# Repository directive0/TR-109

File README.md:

#
This repository hosts a set of design documents for the TR-109 Mark I Picorder. A Picorder is a Raspberry Pi based handheld device that records and displays sensor data for immediate analysis. The TR-109 is designed to use a Raspberry Pi Zero W, a set of custom designed PCBs, and a 3D printed enclosure to achieve this goal. This project, along with [PicorderOS](https://squaredwave.com/wiki/index.php?title=PicorderOS) attempts to be a single self contained solution for anyone wishing to produce their own Picorder.

## What is included:

- The enclosure_design folder contains the .blend file used to produce the STLs for the case, diffusers and spacers. It also contains the main STLs ready to be printed, and an svg file to produce your own stickers.

- The pcb_design folder contains KiCad 5.1.10 files of both the main board, sensor board and indicator board pcbs. These files can be used to produce and test PCBs. There is some PCBWay files that may be useful with their Assembly service, but this is not finalized and may not work properly.

## What is not yet included:

- There are no assembly instructions. I hope to produce some in the future.

While it is not required, if you make a picorder using this repository I would appreciate you sharing photos or videos your build with me at chris@squaredwave.com.

For a more regularly updated description of this project please visit the [wiki](https://squaredwave.com/wiki/index.php?title=Picorder_2)

Originally designed by Chris Barrett in 2021. I consider this project to be "Open Hardware", and as such is free to use, modify distribute or sell. It comes with no promise of support or warranty.

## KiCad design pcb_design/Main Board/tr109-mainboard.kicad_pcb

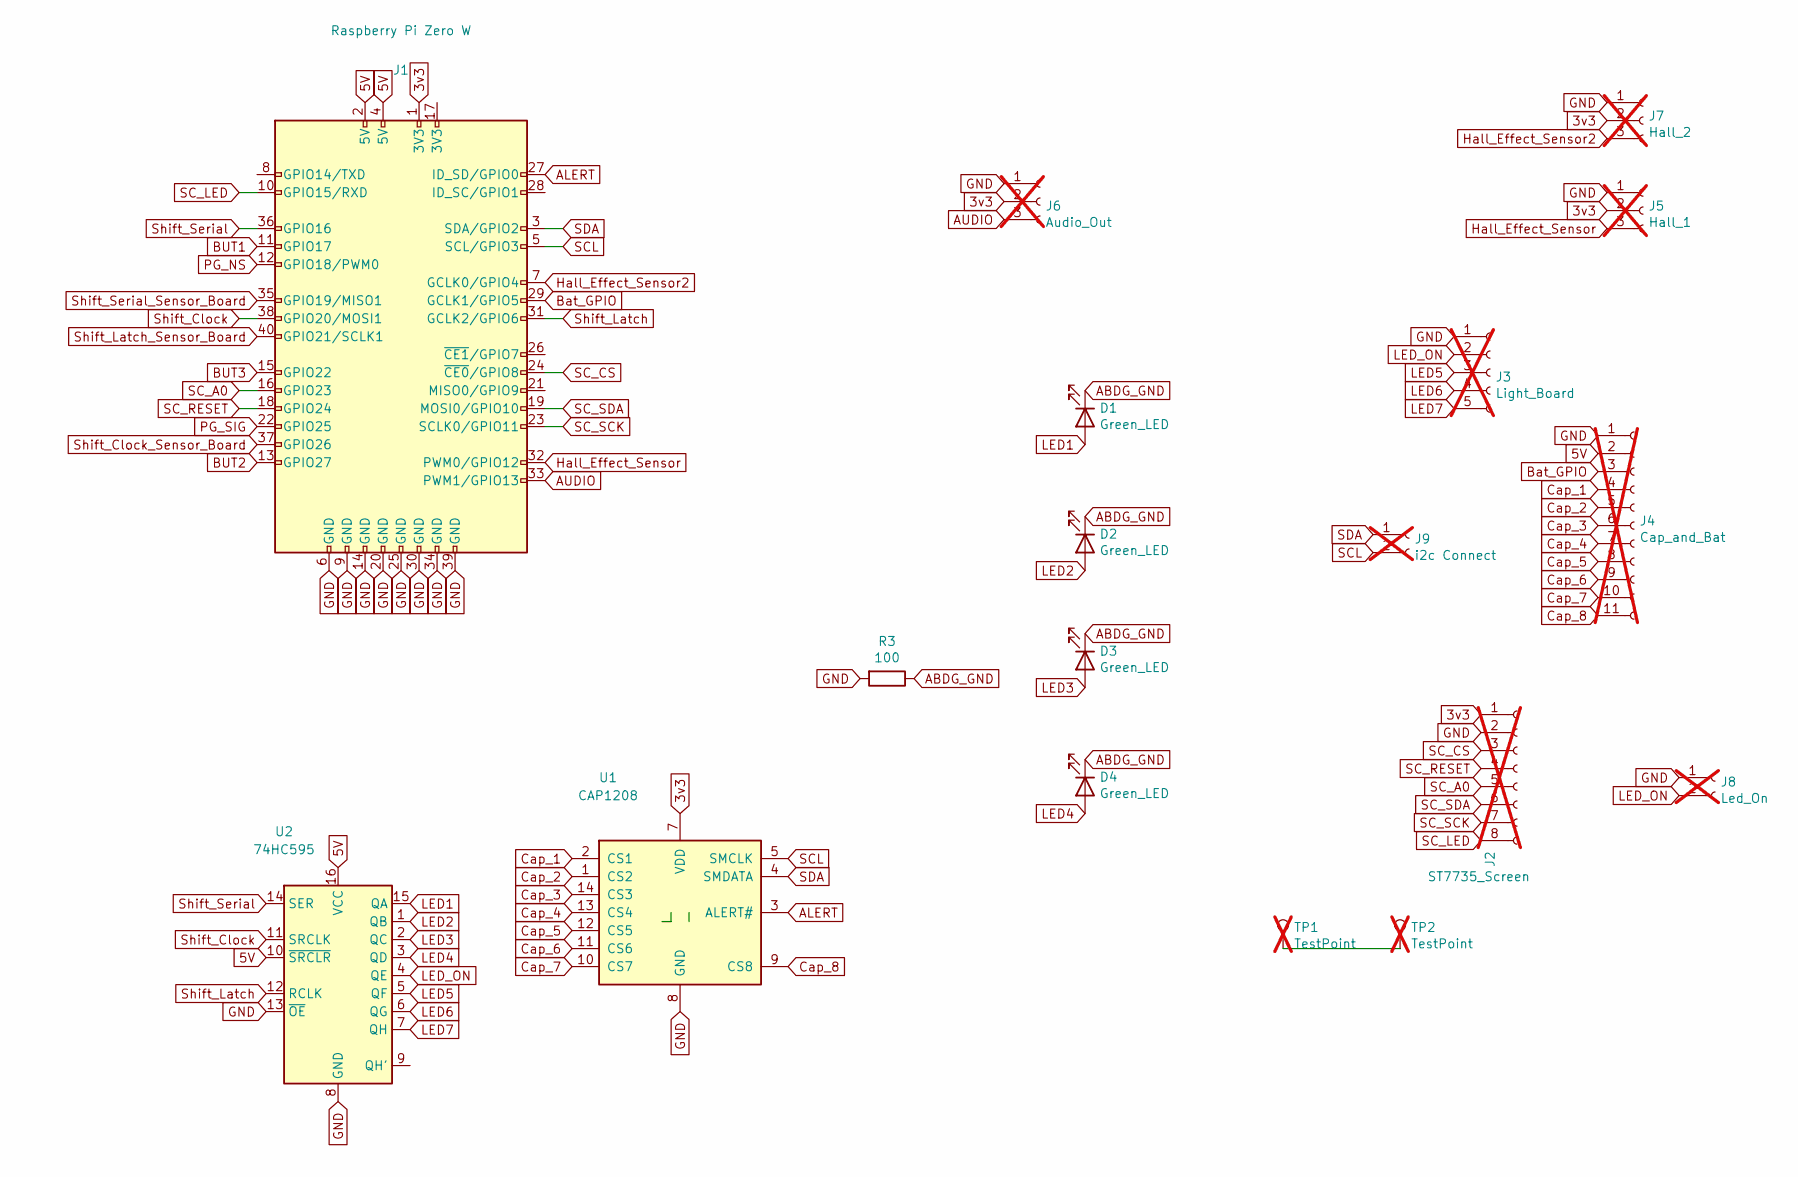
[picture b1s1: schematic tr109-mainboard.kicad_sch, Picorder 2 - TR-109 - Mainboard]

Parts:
D1, D2, D3, D4: Green_LED; LED_D3.0mm
J1: Raspberry Pi Zero W; PinHeader_2x20_P2.54mm_Horizontal
J2: ST7735_Screen; PinHeader_1x08_P2.54mm_Vertical; not fitted
J3: Light_Board; PinHeader_1x05_P2.54mm_Vertical; not fitted
J4: Cap_and_Bat; PinHeader_1x11_P2.54mm_Vertical; not fitted
J5: Hall_1; PinHeader_1x03_P2.54mm_Vertical; not fitted
J6: Audio_Out; PinHeader_1x03_P2.54mm_Vertical; not fitted
J7: Hall_2; PinHeader_1x03_P2.54mm_Vertical; not fitted
J8: Led_On; PinHeader_1x02_P2.54mm_Vertical; not fitted
J9: i2c Connect; PinHeader_1x02_P2.54mm_Vertical; not fitted
R3: 100; R_0805_2012Metric_Pad1.20x1.40mm_HandSolder
TP1, TP2: TestPoint; TestPoint_Pad_1.0x1.0mm; not fitted
U1: CAP1208; SOIC-14_3.9x8.7mm_P1.27mm
U2: 74HC595; SOIC-16_3.9x9.9mm_P1.27mm

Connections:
3v3: J1.1 (3V3), J2.1, J5.2, J6.2, J7.2, U1.7 (VDD)
5V: J1.2 (5V), J1.4 (5V), J4.2, U2.10 (~SRCLR), U2.16 (VCC)
ABDG_GND: D1.1 (K), D2.1 (K), D3.1 (K), D4.1 (K), R3.1
ALERT: J1.27 (ID_SD/GPIO0), U1.3 (ALERT#)
AUDIO: J1.33 (PWM1/GPIO13), J6.3
BUT1: J1.11 (GPIO17)
BUT2: J1.13 (GPIO27)
BUT3: J1.15 (GPIO22)
Bat_GPIO: J1.29 (GCLK1/GPIO5), J4.3
Cap_1: J4.4, U1.2 (CS1)
Cap_2: J4.5, U1.1 (CS2)
Cap_3: J4.6, U1.14 (CS3)
Cap_4: J4.7, U1.13 (CS4)
Cap_5: J4.8, U1.12 (CS5)
Cap_6: J4.9, U1.11 (CS6)
Cap_7: J4.10, U1.10 (CS7)
Cap_8: J4.11, U1.9 (CS8)
GND: J1.6 (GND), J1.9 (GND), J1.14 (GND), J1.20 (GND), J1.25 (GND), J1.30 (GND), J1.34 (GND), J1.39 (GND), J2.2, J3.1, J4.1, J5.1, J6.1, J7.1, J8.1, R3.2, U1.8 (GND), U2.8 (GND), U2.13 (~OE)
Hall_Effect_Sensor: J1.32 (PWM0/GPIO12), J5.3
Hall_Effect_Sensor2: J1.7 (GCLK0/GPIO4), J7.3
LED1: D1.2 (A), U2.15 (QA)
LED2: D2.2 (A), U2.1 (QB)
LED3: D3.2 (A), U2.2 (QC)
LED4: D4.2 (A), U2.3 (QD)
LED5: J3.3, U2.5 (QF)
LED6: J3.4, U2.6 (QG)
LED7: J3.5, U2.7 (QH)
LED_ON: J3.2, J8.2, U2.4 (QE)
unnamed: TP1.1, TP2.1
PG_NS: J1.12 (GPIO18/PWM0)
PG_SIG: J1.22 (GPIO25)
SCL: J1.5 (SCL/GPIO3), J9.2, U1.5 (SMCLK)
SC_A0: J1.16 (GPIO23), J2.5
SC_CS: J1.24 (~CE0/GPIO8), J2.3
SC_LED: J1.10 (GPIO15/RXD), J2.8
SC_RESET: J1.18 (GPIO24), J2.4
SC_SCK: J1.23 (SCLK0/GPIO11), J2.7
SC_SDA: J1.19 (MOSI0/GPIO10), J2.6
SDA: J1.3 (SDA/GPIO2), J9.1, U1.4 (SMDATA)
Shift_Clock: J1.38 (GPIO20/MOSI1), U2.11 (SRCLK)
Shift_Clock_Sensor_Board: J1.37 (GPIO26)
Shift_Latch: J1.31 (GCLK2/GPIO6), U2.12 (RCLK)
Shift_Latch_Sensor_Board: J1.40 (GPIO21/SCLK1)
Shift_Serial: J1.36 (GPIO16), U2.14 (SER)
Shift_Serial_Sensor_Board: J1.35 (GPIO19/MISO1)

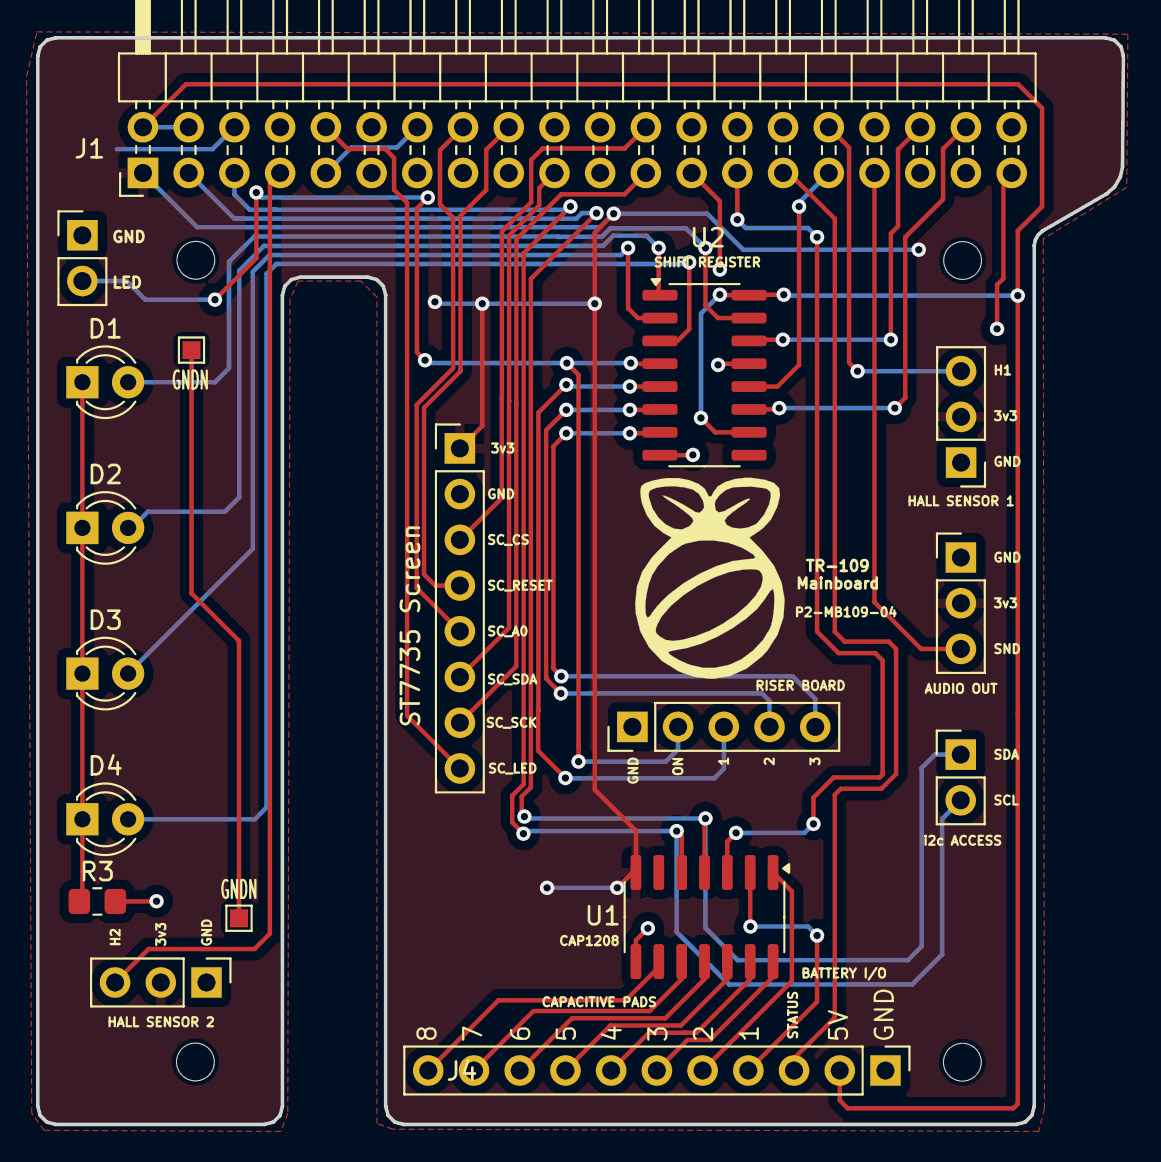
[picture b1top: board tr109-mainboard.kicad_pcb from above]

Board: 2 copper layers, 60.3 x 60.4 mm, 18 parts (0 on the bottom side), 37 nets.

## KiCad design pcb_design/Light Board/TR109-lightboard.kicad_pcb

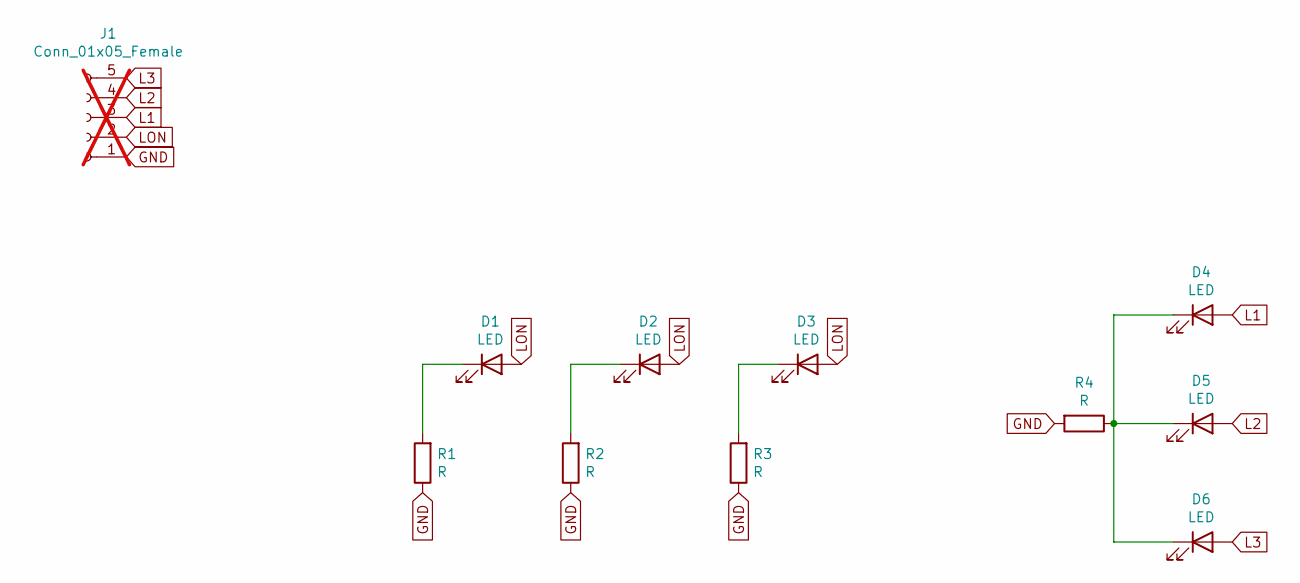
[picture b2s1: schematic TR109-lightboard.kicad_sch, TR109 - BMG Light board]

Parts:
D1, D2, D3, D4, D5, D6: LED; LED_1206_3216Metric_Pad1.42x1.75mm_HandSolder
J1: Conn_01x05_Female; PinHeader_1x05_P2.00mm_Vertical; not fitted
R1, R2, R3, R4: R; R_0805_2012Metric_Pad1.20x1.40mm_HandSolder

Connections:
GND: J1.1, R1.1, R2.1, R3.1, R4.2
L1: D4.2 (A), J1.3
L2: D5.2 (A), J1.4
L3: D6.2 (A), J1.5
LON: D1.2 (A), D2.2 (A), D3.2 (A), J1.2
unnamed: D1.1 (K), R1.2
unnamed: D2.1 (K), R2.2
unnamed: D3.1 (K), R3.2
unnamed: D4.1 (K), D5.1 (K), D6.1 (K), R4.1

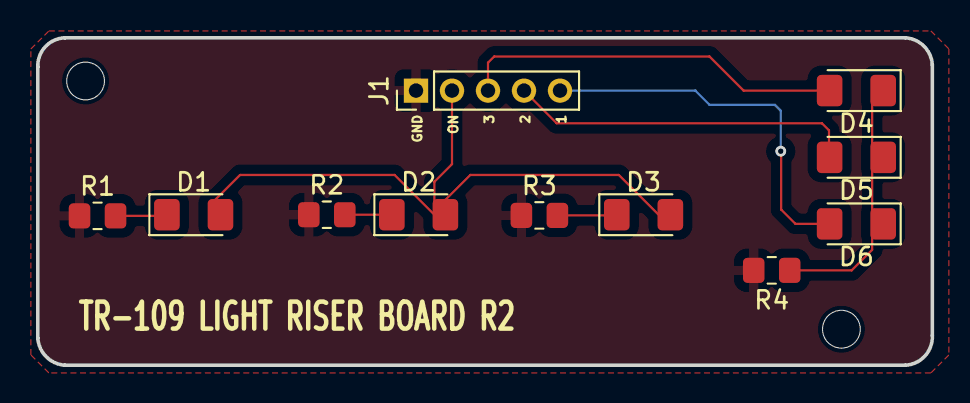
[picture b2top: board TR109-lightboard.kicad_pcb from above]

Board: 2 copper layers, 49.7 x 18.2 mm, 11 parts (0 on the bottom side), 9 nets.

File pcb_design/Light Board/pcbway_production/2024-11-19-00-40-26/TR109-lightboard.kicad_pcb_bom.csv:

Designator,Quantity,Value,Footprint,Package,MPN,DNP,Mount_Type,Colour
"D1, D2, D3, D4, D5, D6",6,LED,LED_1206_3216Metric_Pad1.42x1.75mm_HandSolder,,,,smt,"[D1,D2,D3]Yellow; [D4]Red; [D5,D6]Green"
"R1, R2, R3, R4",4,R,R_0805_2012Metric_Pad1.20x1.40mm_HandSolder,,,,smt,

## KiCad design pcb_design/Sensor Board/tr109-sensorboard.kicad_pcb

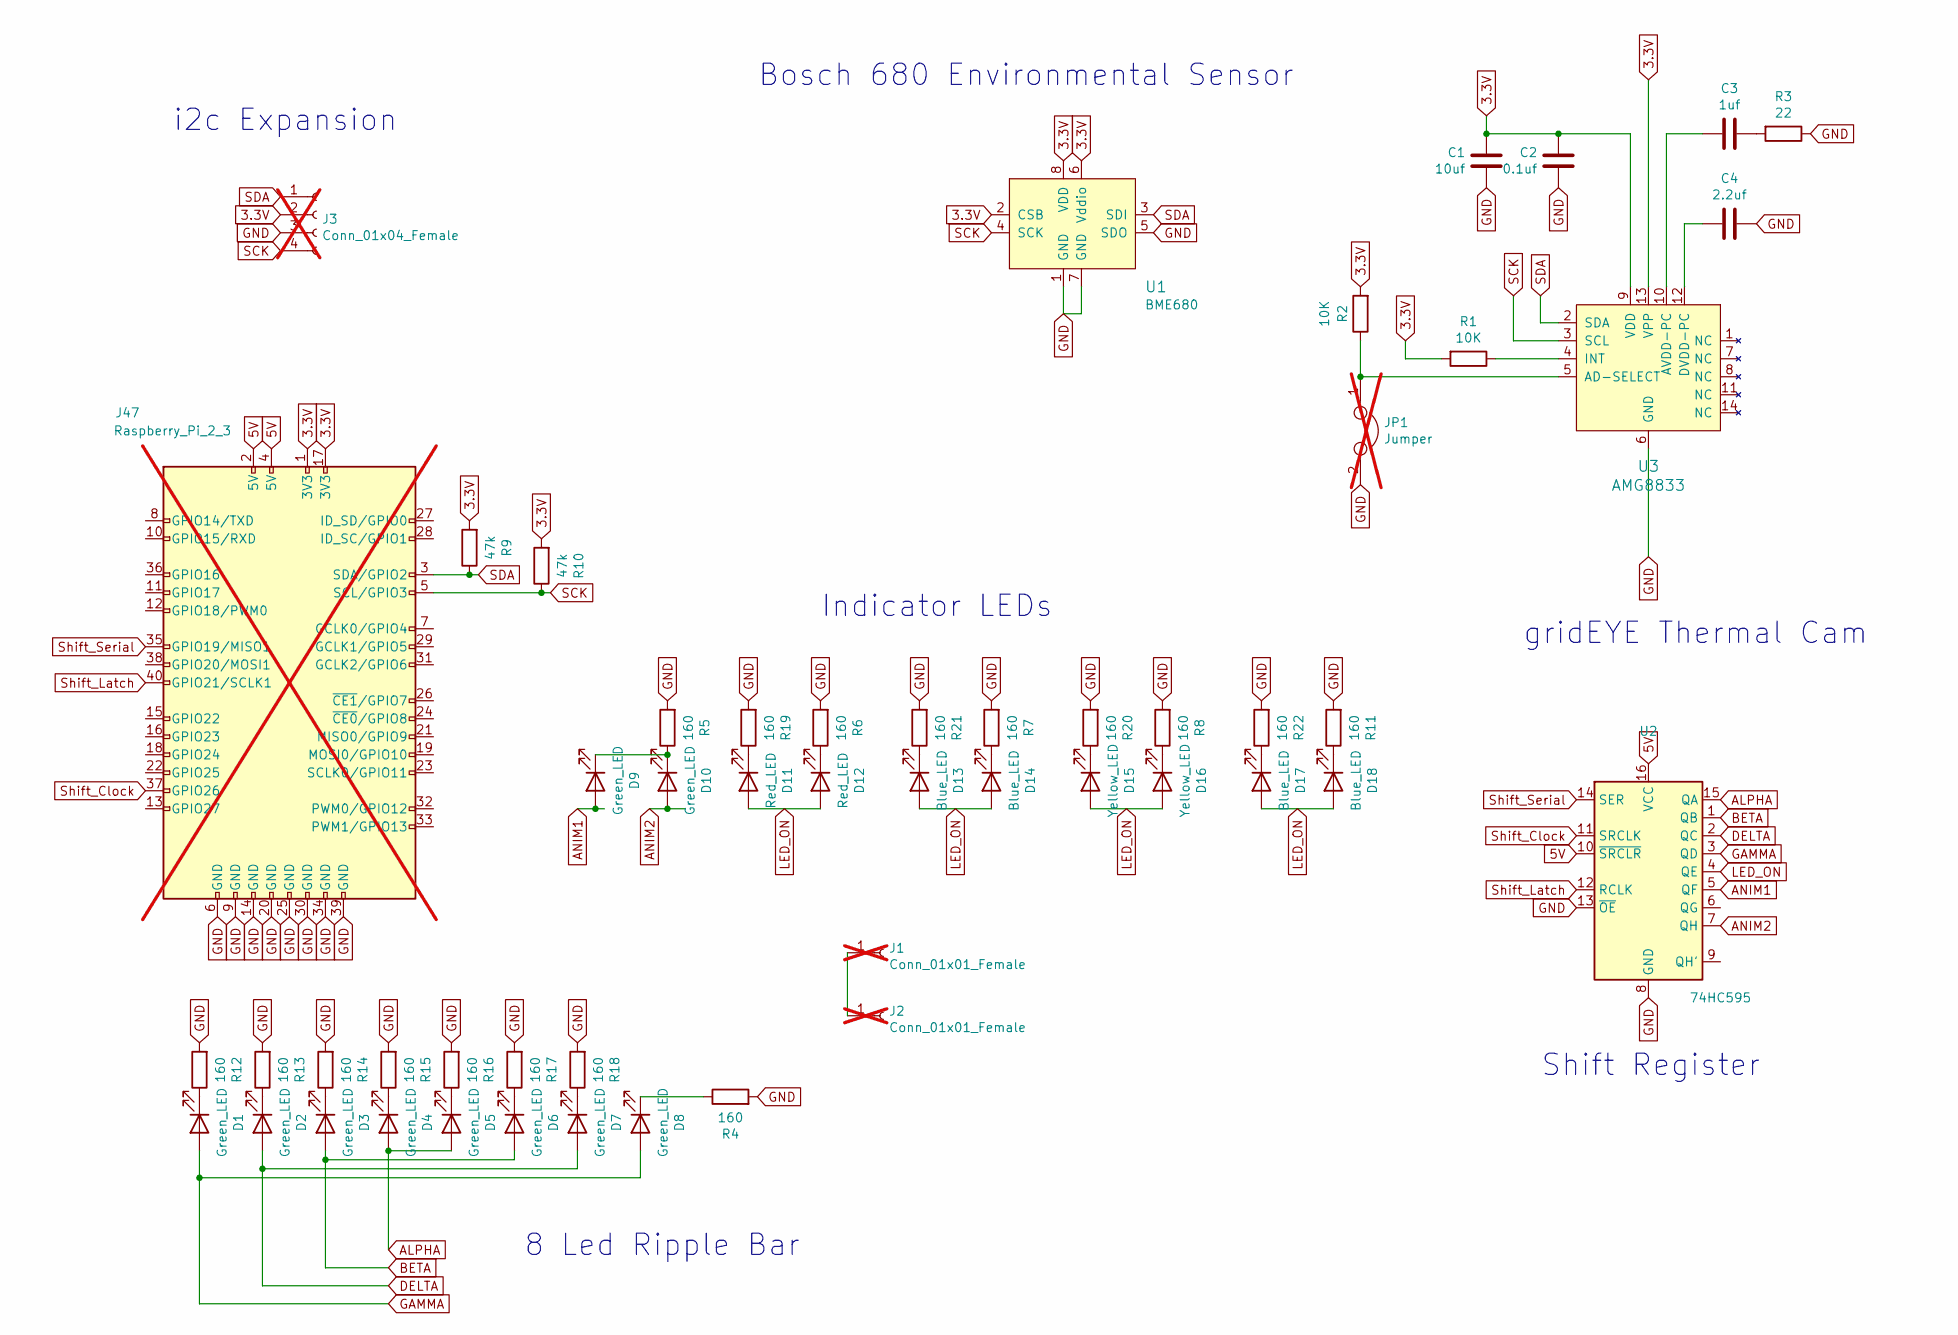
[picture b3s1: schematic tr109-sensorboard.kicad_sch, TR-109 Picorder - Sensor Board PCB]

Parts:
C1: 10uf; C_0805_2012Metric
C2: 0.1uf; C_0805_2012Metric
C3: 1uf; C_0805_2012Metric
C4: 2.2uf; C_0805_2012Metric
D1, D2, D3, D4, D5, D6, D7, D8, D9, D10: Green_LED; LED_1206_3216Metric_Pad1.42x1.75mm_HandSolder
D11, D12: Red_LED; LED_1206_3216Metric_Pad1.42x1.75mm_HandSolder
D13, D14, D17, D18: Blue_LED; LED_1206_3216Metric_Pad1.42x1.75mm_HandSolder
D15, D16: Yellow_LED; LED_1206_3216Metric_Pad1.42x1.75mm_HandSolder
J1, J2: Conn_01x01_Female; TestPoint_Pad_1.0x1.0mm; not fitted
J3: Conn_01x04_Female; PinHeader_1x04_P2.54mm_Vertical; not fitted
J47: Raspberry_Pi_2_3; PinHeader_2x20_P2.54mm_Vertical; not fitted
JP1: Jumper; SolderJumper-2_P1.3mm_Open_Pad1.0x1.5mm; not fitted
R1, R2: 10K; R_0805_2012Metric_Pad1.15x1.40mm_HandSolder
R3: 22; R_0805_2012Metric_Pad1.15x1.40mm_HandSolder
R4, R5, R6, R7, R8, R11, R12, R13, R14, R15, R16, R17, R18, R19, R20, R21, R22: 160; R_0805_2012Metric_Pad1.15x1.40mm_HandSolder
R9, R10: 47k; R_0805_2012Metric_Pad1.15x1.40mm_HandSolder
U1: BME680; MPN BME680; Digi-Key_PN 828-1077-1-ND
U2: 74HC595; SOIC-16_3.9x9.9mm_P1.27mm
U3: AMG8833; SMD-14_Grideye; MPN AMG8833; Digi-Key_PN P19002CT-ND

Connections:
3.3V: C1.2, C2.2, J3.2, J47.1 (3V3), J47.17 (3V3), R1.2, R2.2, R9.2, R10.2, U1.2 (CSB), U1.6 (Vddio), U1.8 (VDD), U3.9 (VDD), U3.13 (VPP)
5V: J47.2 (5V), J47.4 (5V), U2.10 (~SRCLR), U2.16 (VCC)
ALPHA: D4.2 (A), D5.2 (A), U2.15 (QA)
ANIM1: D9.2 (A), U2.5 (QF)
ANIM2: D10.2 (A), U2.7 (QH)
BETA: D3.2 (A), D6.2 (A), U2.1 (QB)
DELTA: D2.2 (A), D7.2 (A), U2.2 (QC)
GAMMA: D1.2 (A), D8.2 (A), U2.3 (QD)
GND: C1.1, C2.1, C4.2, J3.3, J47.6 (GND), J47.9 (GND), J47.14 (GND), J47.20 (GND), J47.25 (GND), J47.30 (GND), J47.34 (GND), J47.39 (GND), JP1.2, R3.1, R4.2, R5.2, R6.2, R7.2, R8.2, R11.2, R12.2, R13.2, R14.2, R15.2, R16.2, R17.2, R18.2, R19.2, R20.2, R21.2, R22.2, U1.1 (GND), U1.5 (SDO), U1.7 (GND), U2.8 (GND), U2.13 (~OE), U3.6 (GND)
LED_ON: D11.2 (A), D12.2 (A), D13.2 (A), D14.2 (A), D15.2 (A), D16.2 (A), D17.2 (A), D18.2 (A), U2.4 (QE)
unnamed: C3.2, R3.2
unnamed: D1.1 (K), R12.1
unnamed: D2.1 (K), R13.1
unnamed: D3.1 (K), R14.1
unnamed: D4.1 (K), R15.1
unnamed: D5.1 (K), R16.1
unnamed: D6.1 (K), R17.1
unnamed: D7.1 (K), R18.1
unnamed: D8.1 (K), R4.1
unnamed: D9.1 (K), D10.1 (K), R5.1
unnamed: D11.1 (K), R19.1
unnamed: D12.1 (K), R6.1
unnamed: D13.1 (K), R21.1
unnamed: D14.1 (K), R7.1
unnamed: D15.1 (K), R20.1
unnamed: D16.1 (K), R8.1
unnamed: D17.1 (K), R22.1
unnamed: D18.1 (K), R11.1
unnamed: J1.1, J2.1
unnamed: JP1.1, R2.1, U3.5 (AD-SELECT)
unnamed: C3.1, U3.10 (AVDD-PC)
unnamed: C4.1, U3.12 (DVDD-PC)
unnamed: R1.1, U3.4 (INT)
SCK: J3.4, J47.5 (SCL/GPIO3), R10.1, U1.4 (SCK), U3.3 (SCL)
SDA: J3.1, J47.3 (SDA/GPIO2), R9.1, U1.3 (SDI), U3.2 (SDA)
Shift_Clock: J47.37 (GPIO26), U2.11 (SRCLK)
Shift_Latch: J47.40 (GPIO21/SCLK1), U2.12 (RCLK)
Shift_Serial: J47.35 (GPIO19/MISO1), U2.14 (SER)

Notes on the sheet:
Indicator LEDs
i2c Expansion
gridEYE Thermal Cam
Shift Register
8 Led Ripple Bar
Bosch 680 Environmental Sensor

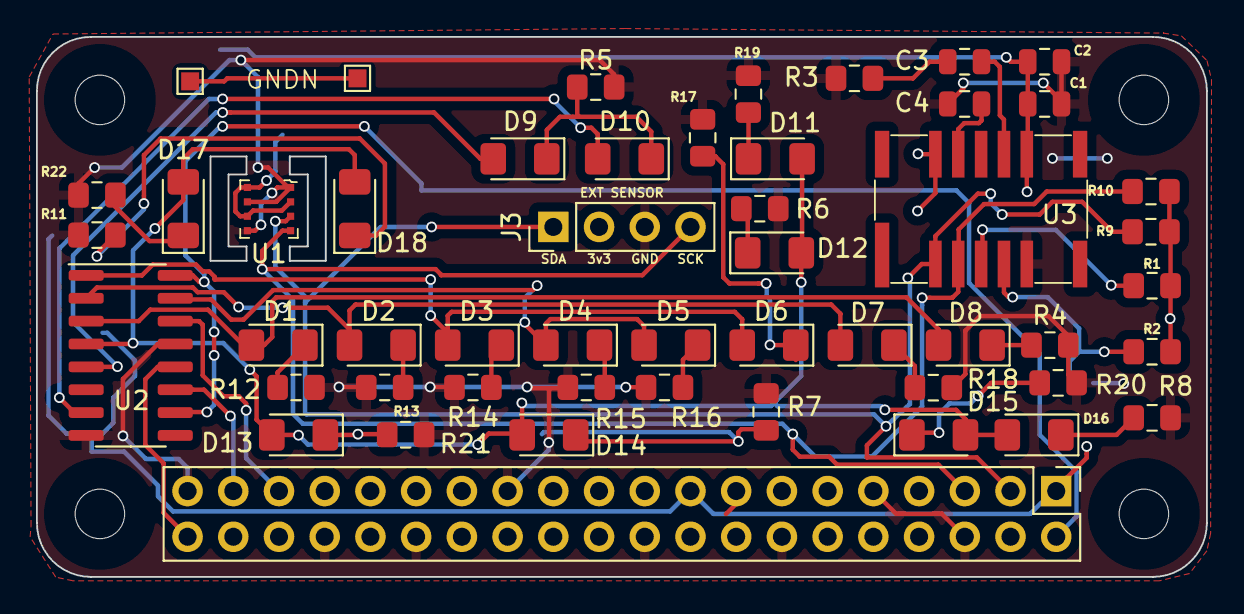
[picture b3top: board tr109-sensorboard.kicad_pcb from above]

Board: 2 copper layers, 65.0 x 30.0 mm, 52 parts (1 on the bottom side), 38 nets.

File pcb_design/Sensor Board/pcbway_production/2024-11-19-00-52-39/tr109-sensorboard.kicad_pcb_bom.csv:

Designator,Quantity,Value,Footprint,Package,MPN,DNP,Mount_Type,Colour,Description,Category,DK_Datasheet_Link,DK_Detail_Page,Digi-Key_PN,Family,Manufacturer,Status
C1,1,10uf,C_0805_2012Metric,,,,smt,,,,,,,,,
C2,1,0.1uf,C_0805_2012Metric,,,,smt,,,,,,,,,
C3,1,1uf,C_0805_2012Metric,,,,smt,,,,,,,,,
C4,1,2.2uf,C_0805_2012Metric,,,,smt,,,,,,,,,
"D1, D10, D2, D3, D4, D5, D6, D7, D8, D9",10,Green_LED,LED_1206_3216Metric_Pad1.42x1.75mm_HandSolder,,,,smt,Green,,,,,,,,
"D11, D12",2,Red_LED,LED_1206_3216Metric_Pad1.42x1.75mm_HandSolder,,,,smt,,,,,,,,,
"D13, D14, D17, D18",4,Blue_LED,LED_1206_3216Metric_Pad1.42x1.75mm_HandSolder,,,,smt,,,,,,,,,
"D15, D16",2,Yellow_LED,LED_1206_3216Metric_Pad1.42x1.75mm_HandSolder,,,,smt,,,,,,,,,
"R1, R2",2,10K,R_0805_2012Metric_Pad1.15x1.40mm_HandSolder,,,,smt,,,,,,,,,
"R10, R9",2,47k,R_0805_2012Metric_Pad1.15x1.40mm_HandSolder,,,,smt,,,,,,,,,
"R11, R12, R13, R14, R15, R16, R17, R18, R19, R20, R21, R22, R4, R5, R6, R7, R8",17,160,R_0805_2012Metric_Pad1.15x1.40mm_HandSolder,,,,smt,,,,,,,,,
R3,1,22,R_0805_2012Metric_Pad1.15x1.40mm_HandSolder,,,,smt,,,,,,,,,
U1,1,BME680,BME680,,BME680,,smt,,SENSOR RH PRESSURE TEMP VOC,"Sensors, Transducers",https://ae-bst.resource.bosch.com/media/_tech/media/datashee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,/product-detail/en/bosch-sensortec/BME680/828-1077-1-ND/7401321,828-1077-1-ND,Specialized Sensors,Bosch Sensortec,Active
U2,1,74HC595,SOIC-16_3.9x9.9mm_P1.27mm,,,,smt,,,,,,,,,
U3,1,AMG8833,SMD-14_Grideye,,AMG8833,,smt,,SENSOR DGTL 14SMD MODULE,"Sensors, Transducers",https://media.digikey.com/pdf/Data%20Sheets/Panasonic%20Sens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,/product-detail/en/panasonic-electronic-components/AMG8833/P19002CT-ND/5825306,P19002CT-ND,Temperature Sensors - Analog and Digital Output,Panasonic Electronic Components,Active

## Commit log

2021-05-02 Initial File Upload
2021-05-02 update to readme
2021-05-02 updates to blend
2021-05-18 Lower door changes
2021-05-25 cleanup and revisions
    changes to the sensor and main boards
    clean up of the blender file to remove some deprecated meshes
2021-05-26 Model improvements.
2021-05-26 blend cleanups
2021-05-28 more case changes
2021-05-28 STL and Blend Changes
    Clean up to Blend file, re-export of STLs for scaling issues
2021-05-28 blend cleanup
2021-05-29 bmg pcb
2021-05-29 refinements to bmg pcb
2021-05-29 sensor board revisions
2021-05-29 sensor board schematic
2021-06-05 pcb and shell changes
2021-06-08 Pcb and shell design work
2021-06-25 Rev 3 board changes, blender file changes
2021-06-25 Kicad Sheet Title Corrections
2021-06-29 more blend changes
2021-07-02 Blender updates.
2021-07-17 Pcb and enclosure changes for proto 01
2021-08-13 changes to shell and pcb
2021-08-23 Unit 01
2021-08-27 parts changes
2022-07-24 Create TR109 - Longer End Cap.stl
    Making an end cap that's roughly 1.69mm longer to allow for use of thicker connectors
2024-11-30 Kicad V8 updates
    Changes to board and improvements. Needs Kicad V8 now.
2024-11-30 kicad v8
2024-11-30 kicadv8
2025-04-25 Updated PCBs
2025-06-26 Fixed some kicad PCB errors, updated Blender file
